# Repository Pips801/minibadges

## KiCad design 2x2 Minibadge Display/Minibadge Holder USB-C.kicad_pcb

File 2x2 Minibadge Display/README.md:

# 2x2 Minibadge Display
## Pictures

## Diagram

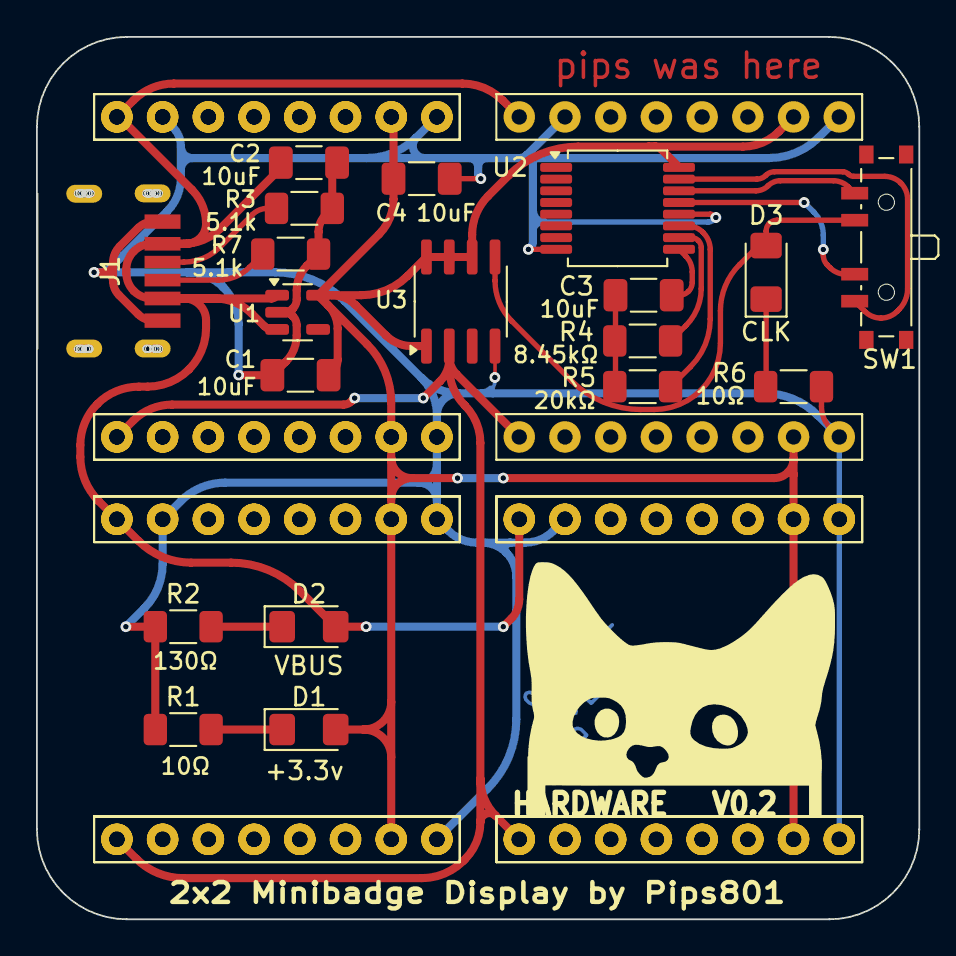
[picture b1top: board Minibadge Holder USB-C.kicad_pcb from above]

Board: 2 copper layers, 49.0 x 49.0 mm, 26 parts (0 on the bottom side), 16 nets.

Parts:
C1, C2: 10uF; C_1206_3216Metric_Pad1.33x1.80mm_HandSolder
C3: 0.1uF; C_1206_3216Metric_Pad1.33x1.80mm_HandSolder
C4: 0.01uF; C_1206_3216Metric_Pad1.33x1.80mm_HandSolder
D1: LED_3.3; LED_1206_3216Metric_Pad1.42x1.75mm_HandSolder
D2: LED_VBUS; LED_1206_3216Metric_Pad1.42x1.75mm_HandSolder
D3: LED_CLK; LED_1206_3216Metric_Pad1.42x1.75mm_HandSolder
J1: TYPE-C-31-M-17; TYPEC31M17
MB1, MB1#2, MB1#3, MB1#4, MB2, MB3, MB4: MiniBadge_Full; MiniBadge_Slot_Basic
R1, R6: 10Ω; R_1206_3216Metric_Pad1.30x1.75mm_HandSolder
R2: 130; R_1206_3216Metric_Pad1.30x1.75mm_HandSolder
R3, R7: 5.1k; R_1206_3216Metric_Pad1.30x1.75mm_HandSolder
R4: 8.45kΩ; R_1206_3216Metric_Pad1.30x1.75mm_HandSolder
R5: 20k; R_1206_3216Metric_Pad1.30x1.75mm_HandSolder
SW1: SW_SP3T; SW_SP3T_PCM13
U1: AP2112K-3.3; SOT-23-5
U2: 74HC4060; SSOP-16_5.3x6.2mm_P0.65mm
U3: TPM8837C; SOIC-8_3.9x4.9mm_P1.27mm

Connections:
+3.3V: C1.1, C4.1, D1.2 (A), MB1#4.7 (+3V3), MB1#4.15 (3V3+), MB2.7 (+3V3), MB2.15 (3V3+), MB3.7 (+3V3), MB3.15 (3V3+), MB4.7 (+3V3), MB4.15 (3V3+), U1.5 (VOUT), U2.16 (VDD), U3.1 (VM), U3.6 (IN1), U3.7 (~SLEEP), U3.8 (VCC)
/CC: J1.A5 (CC1), J1.B5 (CC2), R3.2, R7.2
CLK: MB1#4.9 (CLK), MB2.9 (CLK), MB3.9 (CLK), MB4.9 (CLK), U3.2 (OUT1)
CLK_LOW: D3.2 (A), SW1.3, U3.5 (IN2)
GND: C1.2, C2.2, C4.2, J1.A12 (GND_1), J1.B12 (GND_2), MB1#4.2 (GND), MB1#4.8 (GND), MB1#4.16 (GND), MB2.2 (GND), MB2.8 (GND), MB2.16 (GND), MB3.2 (GND), MB3.8 (GND), MB3.16 (GND), MB4.2 (GND), MB4.8 (GND), MB4.16 (GND), R1.1, R2.1, R3.1, R6.1, R7.1, U1.2 (GND), U2.8 (VSS), U2.12 (CLR), U3.4 (GND)
unnamed: C3.1, R4.1, R5.1
unnamed: D1.1 (K), R1.2
unnamed: D2.1 (K), R2.2
unnamed: D3.1 (K), R6.2
unnamed: SW1.4, U2.14 (Q8)
unnamed: SW1.2, U2.13 (Q9)
unnamed: SW1.1, U2.15 (Q10)
unnamed: C3.2, U2.9 (~Φ0)
unnamed: R5.2, U2.11 (~Φ1)
unnamed: R4.2, U2.10 (Φ0)
VBUS: C2.1, D2.2 (A), J1.A9 (VBUS_1), J1.B9 (VBUS_2), MB1#4.1 (+VBATT), MB2.1 (+VBATT), MB3.1 (+VBATT), MB4.1 (+VBATT), U1.1 (VIN), U1.3 (EN)

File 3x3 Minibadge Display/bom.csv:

Designator,Footprint,Quantity,Value,LCSC Part #
"C1, C2",1206,2,10uF,
C3,1206,1,0.1uF,
C4,1206,1,0.01uF,
D1,1206,1,LED_3.3,C5356080
D2,1206,1,LED_VBUS,C5356080
D3,1206,1,LED_CLK,C5356080
"R1, R6",1206,2,10Ω,
R2,1206,1,130Ω,
"R3, R7",1206,2,5.1kΩ,C163372
R4,1206,1,8.45kΩ,
R5,1206,1,20kΩ,
SW1,SW_SPDT_PCM12,1,ON/OFF,C136659
SW2,SW_SPDT_PCM12,1,CLOCK SPEED,C136659
U1,SOT-23-5,1,AP2112K-3.3,C51118
U2,74LV4060D118,1,74HC4060D,C548000
U3,SOIC-8_3.9x4.9mm_P1.27mm,1,TPM8837C,
USB1,TYPEC31M17,1,TYPE-C-31-M-17,C283540

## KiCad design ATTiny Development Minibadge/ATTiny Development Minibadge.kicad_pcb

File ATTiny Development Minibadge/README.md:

# ATtiny DEVBOARD
## Images
Images may not reflect the latest board revision being sold. Source files are up to date.

## Description
ATTiny-816 Minibadge Devboard with breakouts for USART, I2C, DAC, and SPI, as well as two LEDs. There is also support for two ADC (analog to digital conversion) inputs and two PTC (touch sense) pins. It is programmed using UPDI via pin 6 (PROG4).
## Assembly
Solder top and bottom pin rows. Solder wires directly to pin holes, or use your own pin headers or sockets.
## Setup and code
By default, the ATTiny Devboard will come with some default code flashed (which is in this repository) that will blink PIPS WAS HERE in morse code. To flash, you will need a cheapo $7 UPDI programmer. I use the [Adafruit UPDI friend](https://www.adafruit.com/product/5879). Download the MegaTinyCore library for Arduino and set it up, selecting the 816. Write your code, consulting the circuit diagram for specific pins. I recommend referencing the pins by their chip pinout name, rather than number. Example: `PIN_PB2` (for LEDs)

In the Arduino IDE, make the following changes
* Programmer: SerialUPDI - SLOW 57600 Baud
* Chip: ATtiny816
* Clock: 10Mhz Internal
  
You should then be able to do Sketch -> Upload Using Programmer if your UPDI programmer is connected to UPDI, 3v, and GND (all next to eachother)

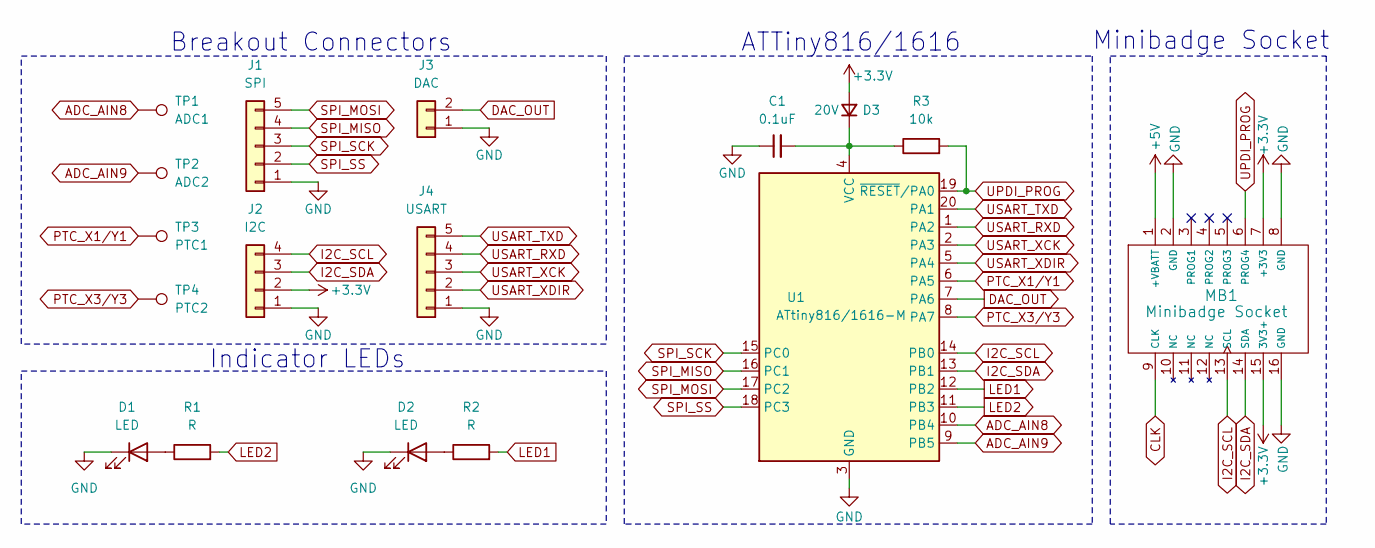
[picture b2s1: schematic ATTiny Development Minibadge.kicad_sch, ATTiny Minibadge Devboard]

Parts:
C1: 0.1uF; C_0603_1608Metric
D1, D2: LED; LED_0603_1608Metric
D3: 20V; D_0603_1608Metric
J1: SPI; PinHeader_1x05_P2.54mm_Vertical
J2: I2C; PinHeader_1x04_P2.54mm_Vertical
J3: DAC; PinHeader_1x02_P2.54mm_Vertical
J4: USART; PinHeader_1x05_P2.54mm_Vertical
MB1: Minibadge Socket; MiniBadge_Full
R1, R2: R; R_0603_1608Metric
R3: 10k; R_0603_1608Metric
TP1: ADC1; TestPoint_Pad_D1.5mm
TP2: ADC2; TestPoint_Pad_D1.5mm
TP3: PTC1; TestPoint_Pad_D1.5mm
TP4: PTC2; TestPoint_Pad_D1.5mm
U1: ATtiny816/1616-M; VQFN-20-1EP_3x3mm_P0.4mm_EP1.7x1.7mm

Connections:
+3.3V: D3.2 (A), J2.2, MB1.7 (+3V3), MB1.15 (3V3+)
+5V: MB1.1 (+VBATT)
ADC_AIN8: TP1.1, U1.10 (PB4)
ADC_AIN9: TP2.1, U1.9 (PB5)
CLK: MB1.9 (CLK)
DAC_OUT: J3.2, U1.7 (PA6)
GND: C1.1, D1.1 (K), D2.1 (K), J1.1, J2.1, J3.1, J4.1, MB1.2 (GND), MB1.8 (GND), MB1.16 (GND), U1.3 (GND), U1.21 (GND)
I2C_SCL: J2.4, MB1.13 (SCL), U1.14 (PB0)
I2C_SDA: J2.3, MB1.14 (SDA), U1.13 (PB1)
LED1: R2.2, U1.12 (PB2)
LED2: R1.2, U1.11 (PB3)
unnamed: D1.2 (A), R1.1
unnamed: D2.2 (A), R2.1
unnamed: C1.2, D3.1 (K), R3.1, U1.4 (VCC)
PTC_X1/Y1: TP3.1, U1.6 (PA5)
PTC_X3/Y3: TP4.1, U1.8 (PA7)
SPI_MISO: J1.4, U1.16 (PC1)
SPI_MOSI: J1.5, U1.17 (PC2)
SPI_SCK: J1.3, U1.15 (PC0)
SPI_SS: J1.2, U1.18 (PC3)
UPDI_PROG: MB1.6 (PROG4), R3.2, U1.19 (~RESET/PA0)
USART_RXD: J4.4, U1.1 (PA2)
USART_TXD: J4.5, U1.20 (PA1)
USART_XCK: J4.3, U1.2 (PA3)
USART_XDIR: J4.2, U1.5 (PA4)

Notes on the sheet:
Minibadge Socket
ATTiny816/1616
Breakout Connectors
Indicator LEDs

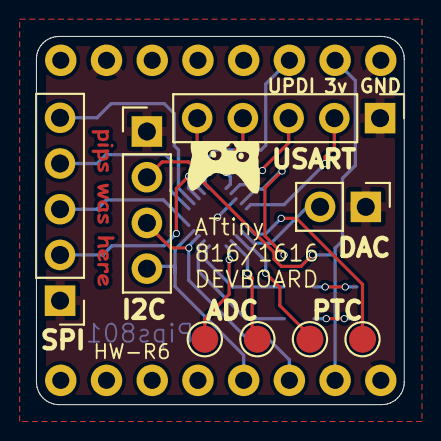
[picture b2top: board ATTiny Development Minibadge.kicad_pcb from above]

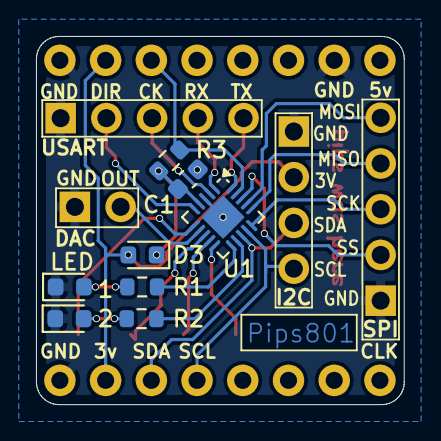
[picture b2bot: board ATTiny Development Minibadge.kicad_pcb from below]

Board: 2 copper layers, 20.4 x 20.5 mm, 17 parts (8 on the bottom side), 23 nets.

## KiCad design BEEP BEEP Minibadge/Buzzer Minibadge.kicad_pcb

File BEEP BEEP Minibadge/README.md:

# BEEP BEEP Minibadge
## Images

## Descrption
An obnoxiously-loud buzzer with an obnoxiously bright and large button. How tempting! Who wouldn't want to press that? Due to the length of the buzzer, the minibadge needs extra-long pin headers to connect snug with the socket.
## Assembly Instructions
First, solder all of the LEDs and resistors. if you are missing R1 (a potentiometer), the simply bridge the pad that says "NO R1" with solder. The potentiometer is meant for volume control. Next, solder the buzzer on the back of the badge, then with some good cutters, snip the leads of the speaker as flush as you can get them. After that, solder the comically large button on the front.

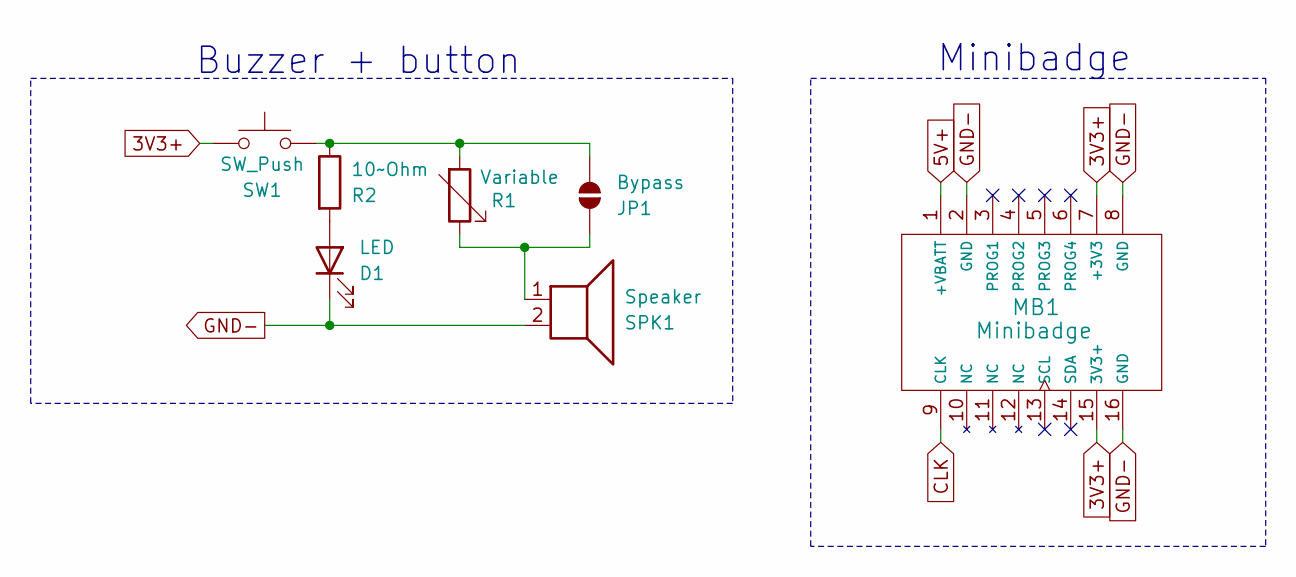
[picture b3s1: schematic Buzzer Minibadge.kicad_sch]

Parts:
D1: LED; LED_1206_3216Metric_Pad1.42x1.75mm_HandSolder
JP1: Bypass; SolderJumper-2_P1.3mm_Open_TrianglePad1.0x1.5mm
MB1: Minibadge; SAINTCON-Minibadge-Simple
R1: Variable; Potentiometer_Bourns_TC33X_Vertical
R2: 10~Ohm; R_1206_3216Metric_Pad1.30x1.75mm_HandSolder
SPK1: Speaker; Buzzer_12x9.5RM7.6
SW1: SW_Push; SW_PUSH-12mm

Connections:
3V3+: MB1.7 (+3V3), MB1.15 (3V3+), SW1.2
5V+: MB1.1 (+VBATT)
CLK: MB1.9 (CLK)
GND-: D1.1 (K), MB1.2 (GND), MB1.8 (GND), MB1.16 (GND), SPK1.2
unnamed: D1.2 (A), R2.2
unnamed: JP1.1 (A), R1.1, SPK1.1
unnamed: JP1.2 (B), R1.2, R2.1, SW1.1

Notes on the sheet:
Minibadge
Buzzer + button

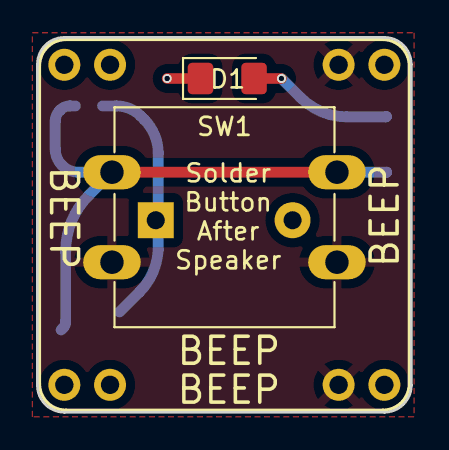
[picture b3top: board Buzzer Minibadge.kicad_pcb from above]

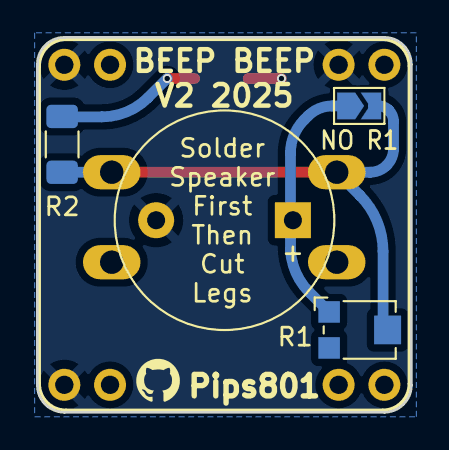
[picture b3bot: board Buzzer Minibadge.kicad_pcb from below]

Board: 2 copper layers, 20.8 x 20.8 mm, 7 parts (4 on the bottom side), 5 nets.

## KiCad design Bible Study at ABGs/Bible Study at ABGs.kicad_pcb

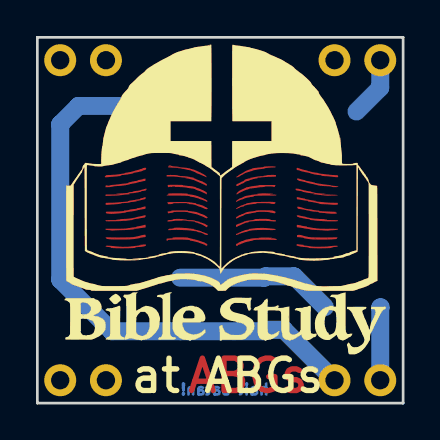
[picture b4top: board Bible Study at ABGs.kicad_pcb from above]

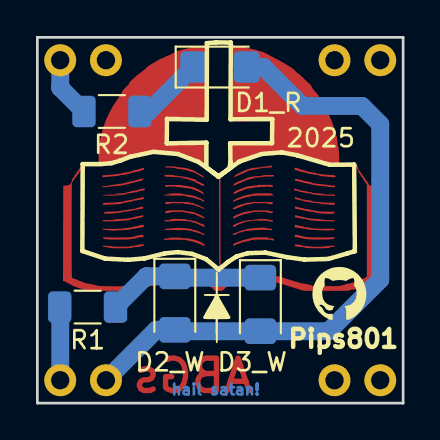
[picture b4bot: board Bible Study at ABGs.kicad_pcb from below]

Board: 2 copper layers, 20.3 x 20.3 mm, 6 parts (5 on the bottom side), 5 nets.

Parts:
D1_R: LED_R; LED_1206_3216Metric_Pad1.42x1.75mm_HandSolder
D2_W, D3_W: LED_W; LED_1206_3216Metric_Pad1.42x1.75mm_HandSolder
R1: R_100Ω; R_1206_3216Metric_Pad1.30x1.75mm_HandSolder
R2: R_10Ω; R_1206_3216Metric_Pad1.30x1.75mm_HandSolder
X1: SAINTCON-Minibadge-Simple

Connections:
unnamed: D1_R.2 (A), D2_W.2 (A), D3_W.2 (A), X1.15 (+3v3)
unnamed: D1_R.1 (K), R2.2
unnamed: D2_W.1 (K), D3_W.1 (K), R1.1
unnamed: R1.2, X1.16 (GND)
unnamed: R2.1, X1.8 (GND)

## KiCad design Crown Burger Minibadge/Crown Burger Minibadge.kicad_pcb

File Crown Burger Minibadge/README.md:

# Crown Burger Minibadge
## Images

## Description
Do you love Fry sauce? because we sure do. We also love Crown Burger, whom we are beholdent to.

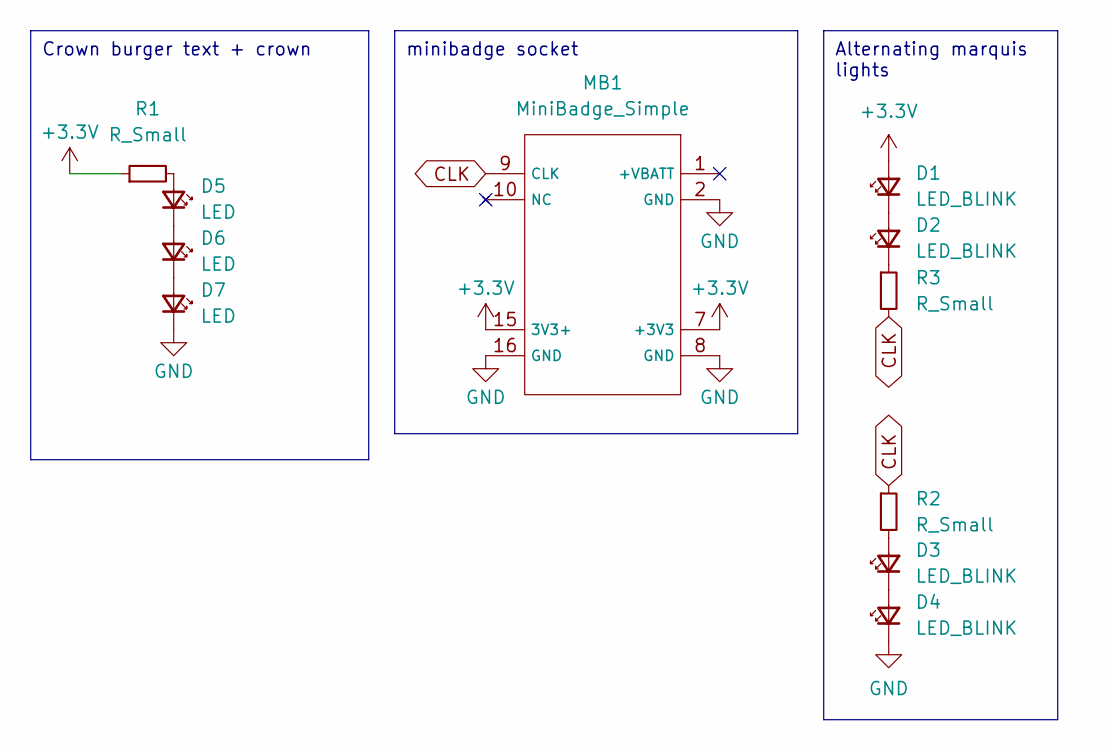
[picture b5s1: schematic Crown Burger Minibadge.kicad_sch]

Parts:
D1, D2, D3, D4: LED_BLINK; LED_0603_1608Metric
D5, D6, D7: LED; LED_0603_1608Metric
MB1: MiniBadge_Simple
R1, R2, R3: R_Small; R_0603_1608Metric

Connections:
+3.3V: D1.2 (A), MB1.7 (+3V3), MB1.15 (3V3+), R1.1
CLK: MB1.9 (CLK), R2.1, R3.2
GND: D4.1 (K), D7.1 (K), MB1.2 (GND), MB1.8 (GND), MB1.16 (GND)
unnamed: D1.1 (K), D2.2 (A)
unnamed: D2.1 (K), R3.1
unnamed: D3.2 (A), R2.2
unnamed: D3.1 (K), D4.2 (A)
unnamed: D5.2 (A), R1.2
unnamed: D5.1 (K), D6.2 (A)
unnamed: D6.1 (K), D7.2 (A)

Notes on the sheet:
Alternating marquis lights
Crown burger text + crown
minibadge socket

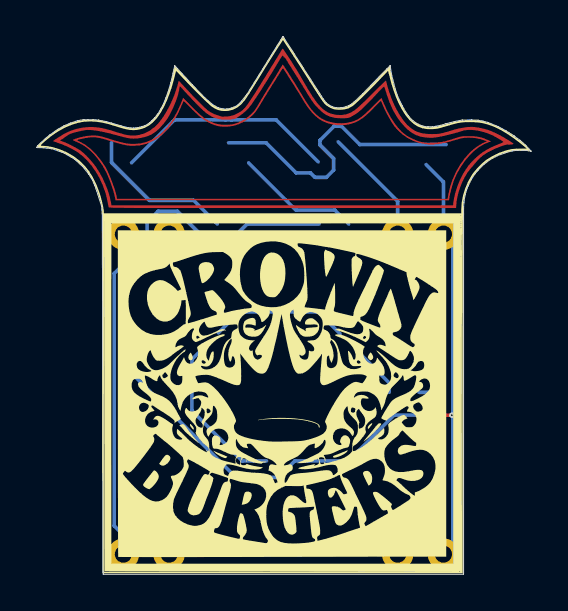
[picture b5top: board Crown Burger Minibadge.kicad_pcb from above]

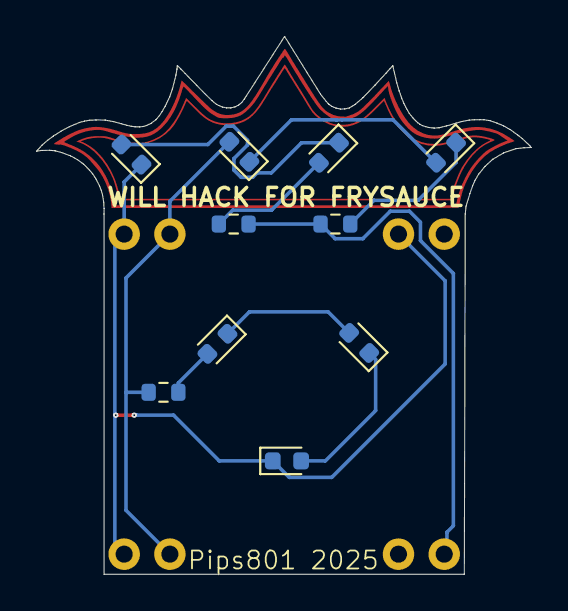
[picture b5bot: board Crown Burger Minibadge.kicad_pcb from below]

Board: 2 copper layers, 27.5 x 29.9 mm, 11 parts (10 on the bottom side), 10 nets.
